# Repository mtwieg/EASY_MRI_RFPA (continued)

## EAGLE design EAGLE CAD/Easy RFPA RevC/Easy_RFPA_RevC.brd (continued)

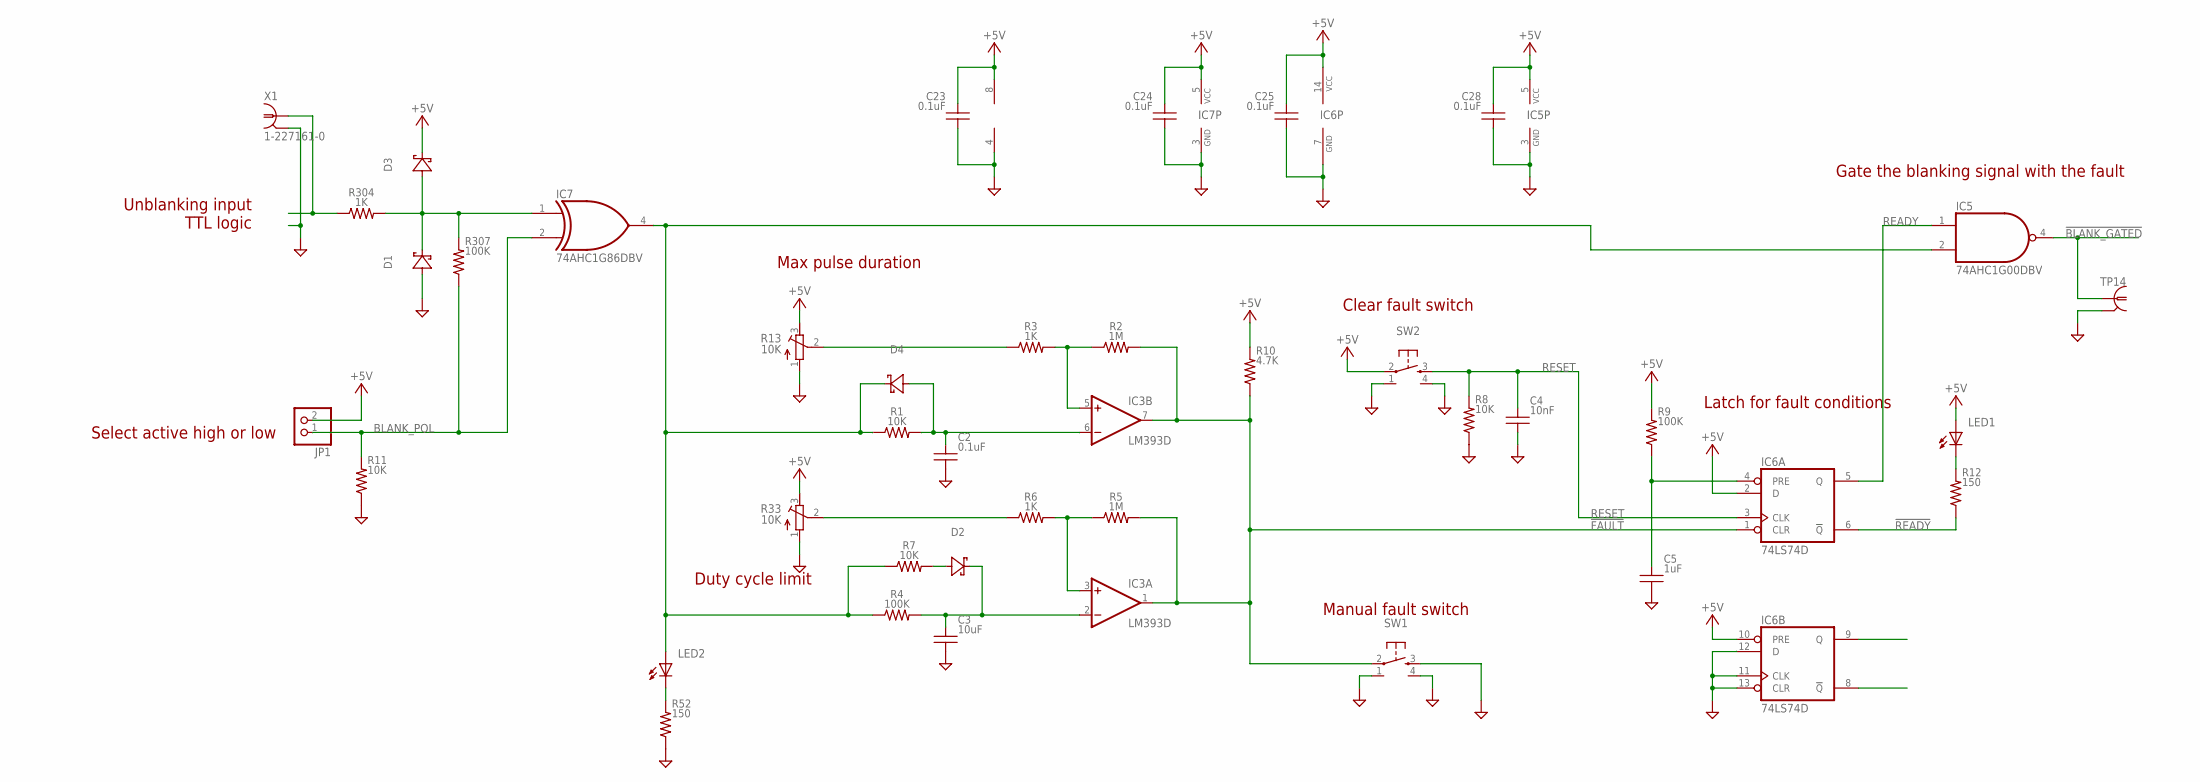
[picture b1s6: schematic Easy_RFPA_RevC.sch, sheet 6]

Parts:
C2, C23, C24, C25, C28: 0.1uF; 0805_IPC-7351B; VOLTAGE 25V
C3: 10uF; 0805_IPC-7351B; VOLTAGE 25V
C4: 10nF; 0805_IPC-7351B; VOLTAGE 50V
C5: 1uF; 0805_IPC-7351B; VOLTAGE 50V
D1, D2, D3, D4: D-SCHOTTKY1N5711W-7-FSOD123; SOD123
IC3: LM393D; SO08
IC5: 74AHC1G00DBV; SOT23-5
IC6: 74LS74D; SO14
IC7: 74AHC1G86DBV; SOT23-5
JP1: PINHD-1X2; 1X02
LED1, LED2: LEDT1_3/4_RA; LED_5MM_RA
R1, R7, R8, R11: 10K; 0805_IPC-7351B
R2, R5: 1M; 0805_IPC-7351B
R3, R6, R304: 1K; 0805_IPC-7351B
R4, R9, R307: 100K; 0805_IPC-7351B
R10: 4.7K; 0805_IPC-7351B
R12, R52: 150; 0805_IPC-7351B
R13, R33: 10K; RTRIM3299W
SW1, SW2: SPST_NO_TACT_RA431256083716431256083716; 431256083716
TP14: PROBE_TPTP_5MM; PROBE_TP_5MM
X1: 1-227161-0; AMP_227161

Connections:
!BLANK_GATED: IC5.4 (O), TP14.TP (1); also elsewhere on the board
!FAULT: IC3.1 (OUT), IC3.7 (OUT), IC6.1 (CLR), R2.2, R5.2, R10.2, SW1.2 (P1)
!READY: IC6.6 (!Q), R12.2
+5V: C23.1, C24.1, C25.1, C28.1, D3.K (C1), IC3.8 (V+), IC5.5 (VCC), IC6.2 (D), IC6.10 (PRE), IC6.14 (VCC), IC7.5 (VCC), JP1.2, LED1.A, R9.1, R10.1, R13.3 (E), R33.3 (E), SW2.2 (P1); also elsewhere on the board
BLANK_POL: IC7.2 (I1), JP1.1, R11.1, R307.2
GND: C2.2, C3.2, C4.2, C5.2, C23.2, C24.2, C25.2, C28.2, D1.A (A1), IC3.4 (V-), IC5.3 (GND), IC6.7 (GND), IC6.11 (CLK), IC6.12 (D), IC6.13 (CLR), IC7.3 (GND), R8.2, R11.2, R13.1 (A), R33.1 (A), R52.2, SW1.1 (G1), SW1.3 (S1), SW1.4 (G2), SW2.1 (G1), SW2.4 (G2), TP14.GND (GND1), X1.2; also elsewhere on the board
unnamed: D1.K (C1), D3.A (A1), IC7.1 (I0), R304.2, R307.1
unnamed: R304.1, X1.1
unnamed: C2.1, D4.A (A1), IC3.6 (-IN), R1.2
unnamed: C5.1, IC6.4 (PRE), R9.2
unnamed: IC3.5 (+IN), R2.1, R3.2
unnamed: R3.1, R13.2 (S)
unnamed: C3.1, D2.K (C1), IC3.2 (-IN), R4.2
unnamed: IC3.3 (+IN), R5.1, R6.2
unnamed: R6.1, R33.2 (S)
unnamed: D4.K (C1), IC5.2 (I1), IC7.4 (O), LED2.A, R1.1, R4.1, R7.1
unnamed: D2.A (A1), R7.2
unnamed: LED2.K (C), R52.1
unnamed: LED1.K (C), R12.1
READY: IC5.1 (I0), IC6.5 (Q)
RESET: C4.1, IC6.3 (CLK), R8.1, SW2.3 (S1)

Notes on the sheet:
Unblanking input TTL logic
Select active high or low
Max pulse duration
Duty cycle limit
Manual fault switch
Clear fault switch
Latch for fault conditions
Gate the blanking signal with the fault

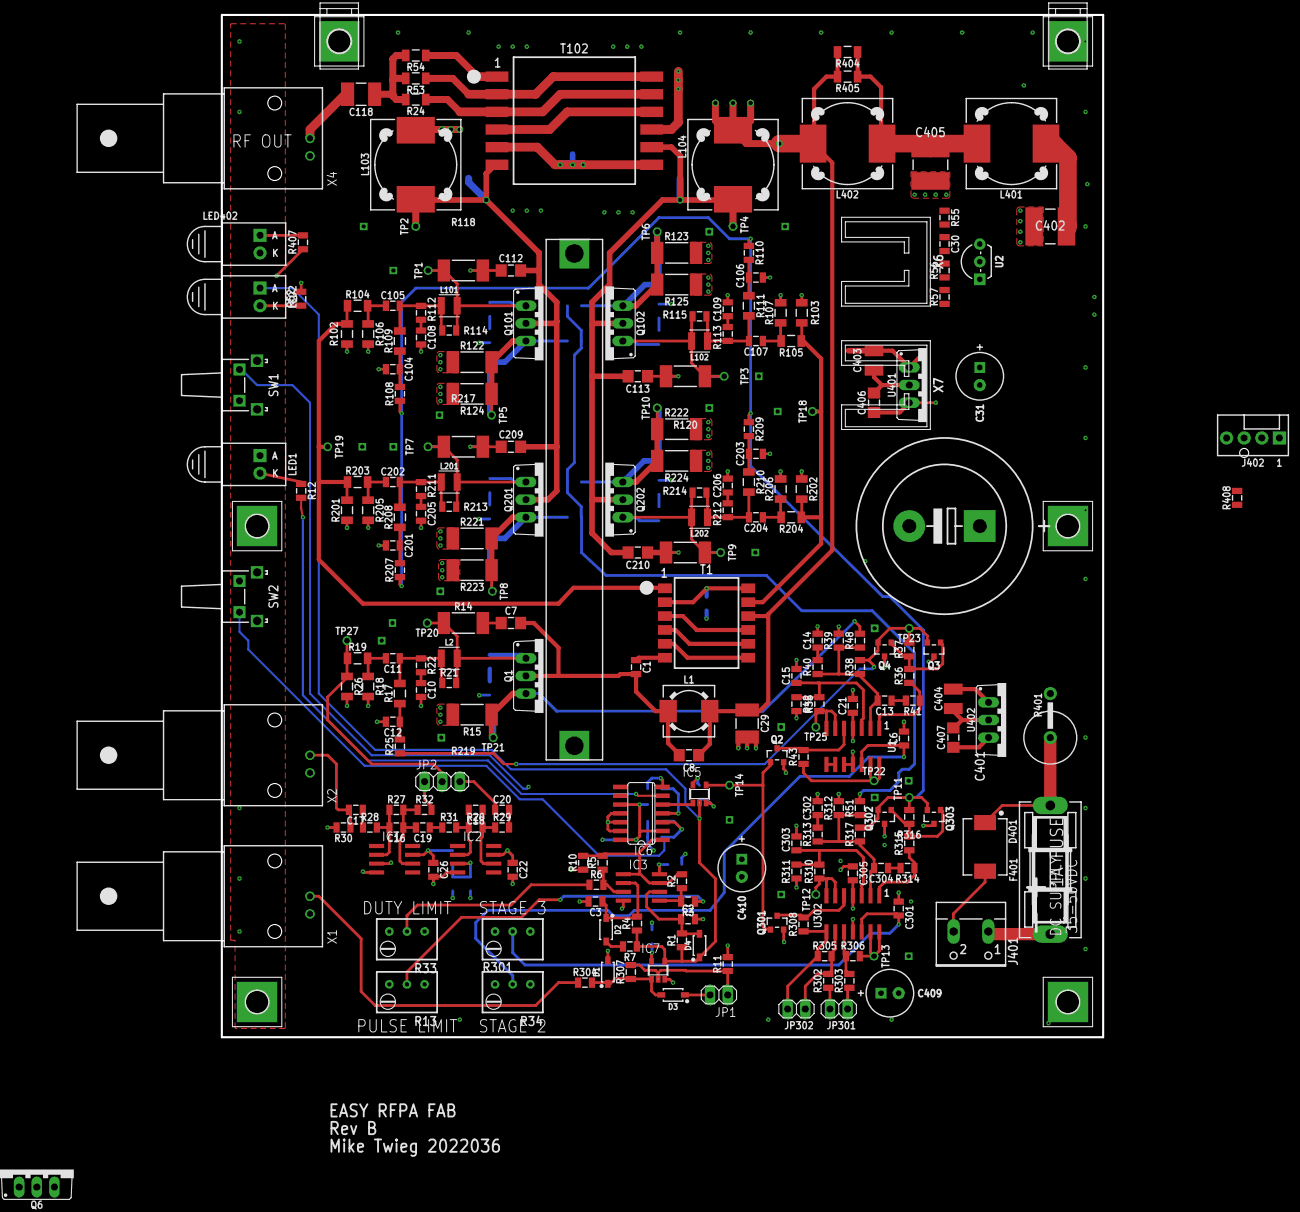
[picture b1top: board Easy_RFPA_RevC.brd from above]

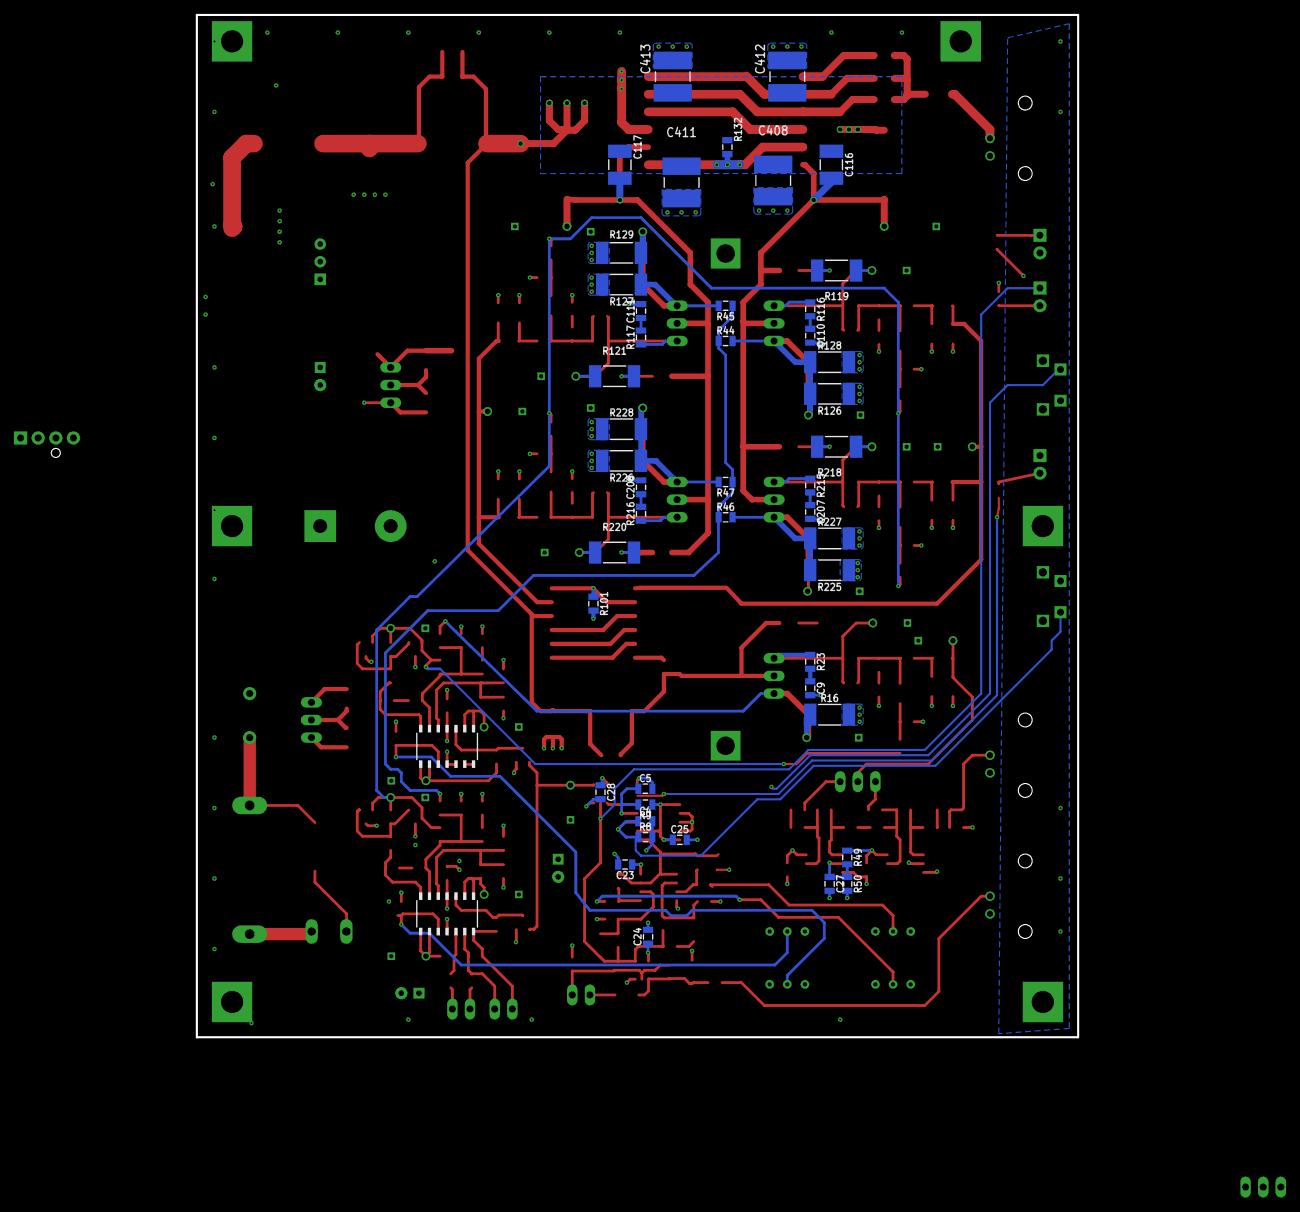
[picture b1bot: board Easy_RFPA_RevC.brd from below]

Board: 4 copper layers, 127.0 x 147.3 mm, 296 parts (46 on the bottom side), 130 nets.

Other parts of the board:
U$1, U$2: KEYSTONE_634

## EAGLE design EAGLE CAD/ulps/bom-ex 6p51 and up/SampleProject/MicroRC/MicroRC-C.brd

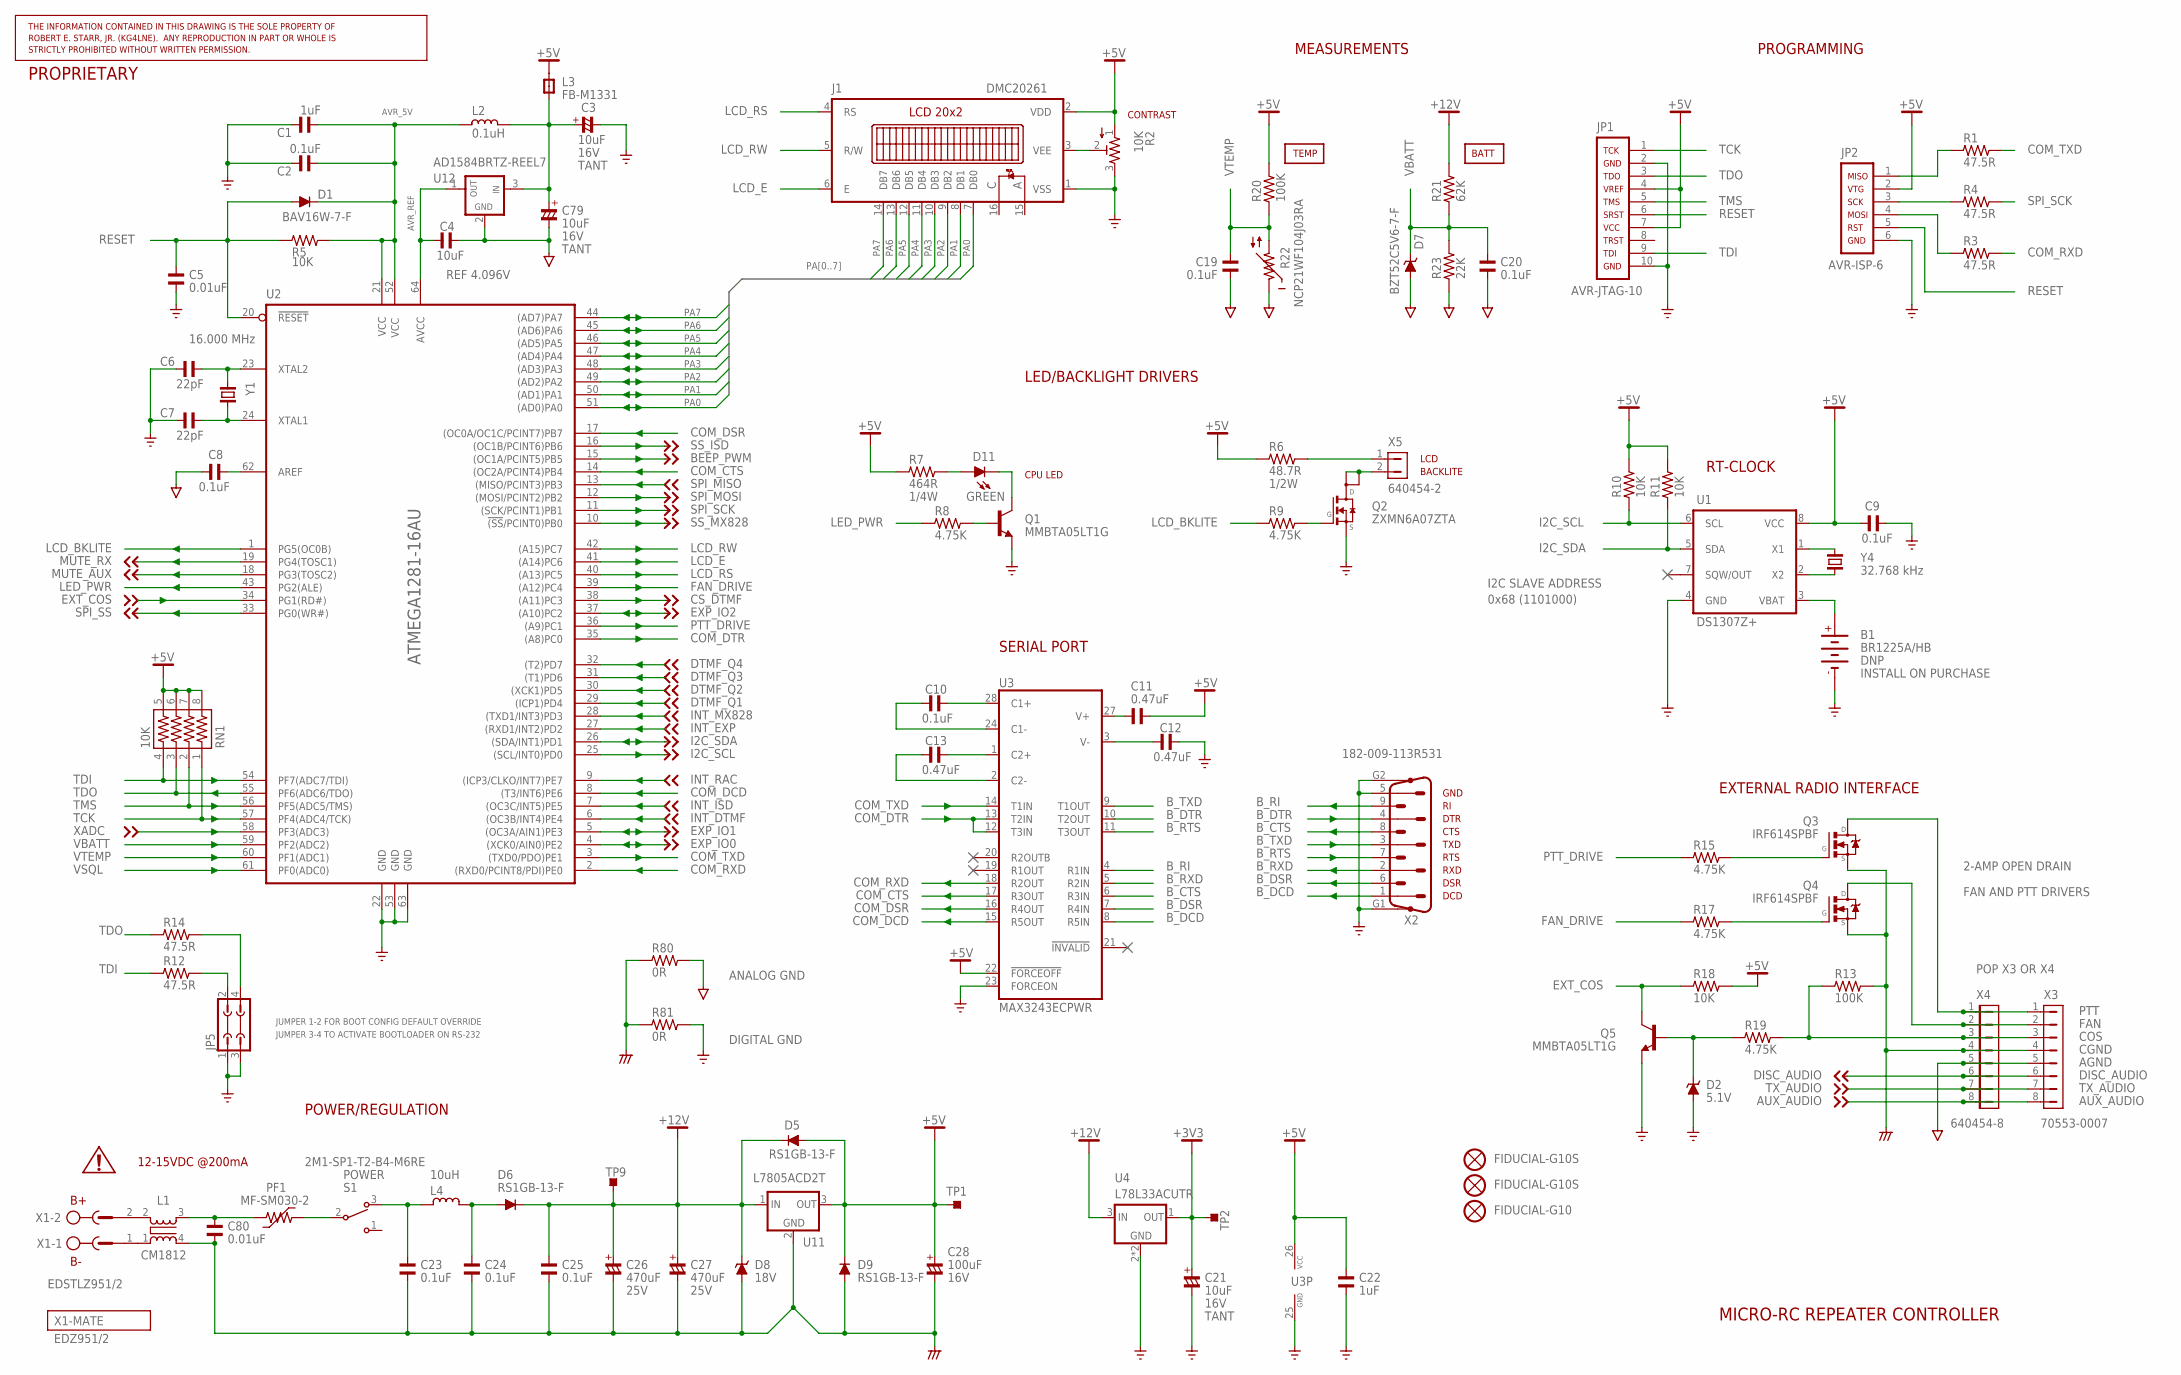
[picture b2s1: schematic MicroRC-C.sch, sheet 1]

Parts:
B1: BR1225A/HB; BR1225; PARTNO BR1225A/HB
C1, C22: 1uF; C0805; PARTNO C0805C105Z3VACTU
C2, C8, C9, C10, C19, C20: 0.1uF; C0805; PARTNO C0805F104K5RACTU
C3, C21, C79: 10uF; C3528/T; PARTNO T491B106M016AT
C4: 10uF; C0805; PARTNO C0805C106K9PACTU
C5: 0.01uF; C0805; PARTNO C0805C103K5RACTU
C6, C7: 22pF; C0805; PARTNO C0805C220J5GACTU
C11, C12, C13: 0.47uF; C0805; PARTNO C0805F474K3RACTU
C23, C24, C25: 0.1uF; C1206; PARTNO C1206C104K5RACTU
C26, C27: 470uF; CSV-G; PARTNO EEE-1EA471P
C28: 100uF; CSV-E/F; PARTNO EEE-1CA101P
C80: 0.01uF; C1206; PARTNO 12065C103KAT2A
D1: BAV16W-7-F; SOD123; PARTNO BAV16W-7-F
D2: 5.1V; SOD123; PARTNO BZT52C5V1-7-F
D5, D6, D9: RS1GB-13-F; SMB; PARTNO RS1GB-13-F
D7: BZT52C5V6-7-F; SOD123; PARTNO BZT52C5V6-7-F
D8: 18V; SMB; PARTNO 1SMB5931BT3G
D11: GREEN; LED535; PARTNO 5350T5
FIDUCIAL1, FIDUCIAL2: FIDUCIAL-G10S; G10S
FIDUCIAL3: FIDUCIAL-G10; G10
J1: DMC20261; PARTNO *
JP1: AVR-JTAG-10; PARTNO *
JP2: AVR-ISP-6
JP5: JP2Q; PARTNO *
L1: CM1812; PARTNO CM1812R600R-10
L2: 0.1uH; L1206; PARTNO PM1210-R10J
L3: FB-M1331; L1206; PARTNO PM2001-200
L4: 10uH; PM-13; PARTNO PM3308-100M
PF1: MF-SM030-2; SMD-7555; PARTNO MF-SM030-2
Q1, Q5: MMBTA05LT1G; SOT23; PARTNO MMBTA05LT1G
Q2: ZXMN6A07ZTA; SOT89; PARTNO ZXMN6A07ZTA
Q3, Q4: IRF614SPBF; D2PAK; PARTNO IRF614SPBF
R1, R3, R4, R12, R14: 47.5R; R0805; PARTNO ERJ-6ENF47R5V
R2: 10K; EVM-L4G; PARTNO EVM-L4GA00B14
R5, R10, R11, R18: 10K; R0805; PARTNO ERJ-6ENF1002V
R6: 48.7R; R2010; PARTNO ERJ-12SF48R7U
R7: 464R; R1210; PARTNO ERJ-14NF4640U
R8, R9, R15, R17, R19: 4.75K; R0805; PARTNO ERJ-6ENF4751V
R13, R20: 100K; R0805; PARTNO ERJ-6ENF1003V
R21: 62K; R0805; PARTNO ERJ-6ENF6192V
R22: NCP21WF104J03RA; R0805; PARTNO NCP21WF104J03RA
R23: 22K; R0805; PARTNO ERJ-6ENF2212V
R80, R81: 0R; R0805; PARTNO RC0805JR-070RL
RN1: 10K; 744-8; PARTNO 744C083103JPTR
S1: 2M1-SP1-T2-B4-M6RE; CK-A; PARTNO 2M1-SP1-T2-B4-M6RE
TP1, TP2, TP9: TPTP10SQ; TP10SQ
U1: DS1307Z+; SO08; PARTNO DS1307Z+
U2: ATMEGA1281-16AU; TQFP64-AEB; PARTNO ATMEGA1281-16AU
U3: MAX3243ECPWR; TSSOP28; PARTNO MAX3243ECPWR
U4: L78L33ACUTR; SOT89-4; PARTNO L78L33ACUTR
U11: L7805ACD2T; D2PAK; PARTNO L7805ACD2T
U12: AD1584BRTZ-REEL7; SOT23; PARTNO AD1584BRTZ-REEL7
X1: EDSTLZ951/2; 951-2; PARTNO EDSTLZ951/2
X2: 182-009-113R531; NC182M9; PARTNO 182-009-113R531
X3: 70553-0007; 70553-08; PARTNO 70553-0007
X4: 640454-8; MTA08-100; PARTNO 640454-8
X5: 640454-2; MTA-100-2V; PARTNO 640454-2
Y1: 16.000 MHz; TC38H; PARTNO ECS-160-18-9X
Y4: 32.768 kHz; TC26H; PARTNO ECS-.327-12.5-13X

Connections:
+3V3: C21.+, TP2.TP, U4.1 (OUT); also elsewhere on the board
+5V: C9.1, C11.1, C22.1, C28.+, D5.A, D9.C, J1.2 (VDD), JP1.4, JP1.7, JP2.2, L3.2, R2.1, R6.1, R7.1, R10.2, R11.2, R18.2, R20.2, RN1.5, RN1.6, RN1.7, RN1.8, TP1.TP, U1.8 (VCC), U3.22 (!FORCEOFF!), U3.26 (VCC), U11.3 (OUT); also elsewhere on the board
+12V: C25.1, C26.+, C27.+, D5.C, D6.C, D8.C, R21.2, TP9.TP, U4.3 (IN), U11.1 (IN); also elsewhere on the board
AGND: C4.1, C8.2, C19.2, C20.2, C79.-, D7.A, R22.1, R23.1, R80.2, U12.2 (GND), X3.5, X4.5; also elsewhere on the board
AUX_AUDIO: X3.8, X4.8; also elsewhere on the board
AVR_5V: C1.1, C2.1, D1.C, L2.2, R5.2, U2.21 (VCC), U2.52 (VCC1)
AVR_REF: C4.2, U2.64 (AVCC), U12.1 (OUT)
BEEP_PWM: U2.15 ((OC1A/PCINT5)PB5); also elsewhere on the board
B_CTS: U3.6 (R3IN), X2.8
B_DCD: U3.8 (R5IN), X2.1
B_DSR: U3.7 (R4IN), X2.6
B_DTR: U3.10 (T2OUT), X2.4
B_RI: U3.4 (R1IN), X2.9
B_RTS: U3.11 (T3OUT), X2.7
B_RXD: U3.5 (R2IN), X2.2
B_TXD: U3.9 (T1OUT), X2.3
CGND: C23.2, C24.2, C25.2, C26.-, C27.-, C28.-, C80.2, D8.A, D9.A, L1.4, Q3.3 (S), Q4.3 (S), R13.2, R80.1, R81.1, U11.2 (GND), X3.4, X4.4
COM_CTS: U2.14 ((OC2A/PCINT4)PB4), U3.17 (R3OUT)
COM_DCD: U2.8 ((T3/INT6)PE6), U3.15 (R5OUT)
COM_DSR: U2.17 ((OC0A/OC1C/PCINT7)PB7), U3.16 (R4OUT)
COM_DTR: U2.35 ((A8)PC0), U3.12 (T3IN), U3.13 (T2IN)
COM_RXD: R3.2, U2.2 ((RXD0/PCINT8/PDI)PE0), U3.18 (R2OUT)
COM_TXD: R1.2, U2.3 ((TXD0/PDO)PE1), U3.14 (T1IN)
COS: R13.1, R19.2, X3.3, X4.3
CS_DTMF: U2.38 ((A11)PC3); also elsewhere on the board
DISC_AUDIO: X3.6, X4.6; also elsewhere on the board
DTMF_Q1: U2.29 ((ICP1)PD4); also elsewhere on the board
DTMF_Q2: U2.30 ((XCK1)PD5); also elsewhere on the board
DTMF_Q3: U2.31 ((T1)PD6); also elsewhere on the board
DTMF_Q4: U2.32 ((T2)PD7); also elsewhere on the board
EXP_IO0: U2.4 ((XCK0/AIN0)PE2); also elsewhere on the board
EXP_IO1: U2.5 ((OC3A/AIN1)PE3); also elsewhere on the board
EXP_IO2: U2.37 ((A10)PC2); also elsewhere on the board
EXT_COS: Q5.3 (C), R18.1, U2.34 (PG1(RD#))
FAN: Q4.2 (D), X3.2, X4.2
FAN_DRIVE: R17.1, U2.39 ((A12)PC4)
GND: B1.-, C1.2, C2.2, C3.-, C5.2, C6.2, C7.2, C9.2, C12.1, C21.-, C22.2, D2.A, J1.1 (VSS), JP1.2, JP1.10, JP2.6, JP5.1, JP5.3, Q1.2 (E), Q2.3 (S), Q5.2 (E), R2.3, R81.2, U1.4 (GND), U2.22 (GND), U2.53 (GND1), U2.63 (GND2), U3.23 (FORCEON), U3.25 (GND), U4.2 (GND), U4.4 (GND), X2.5, X2.G1, X2.G2; also elsewhere on the board
I2C_SCL: R10.1, U1.6 (SCL), U2.25 ((SCL/INT0)PD0); also elsewhere on the board
I2C_SDA: R11.1, U1.5 (SDA), U2.26 ((SDA/INT1)PD1); also elsewhere on the board
INT_DTMF: U2.6 ((OC3B/INT4)PE4); also elsewhere on the board
INT_EXP: U2.27 ((RXD1/INT2)PD2); also elsewhere on the board
INT_ISD: U2.7 ((OC3C/INT5)PE5); also elsewhere on the board
INT_MX828: U2.28 ((TXD1/INT3)PD3); also elsewhere on the board
INT_RAC: U2.9 ((ICP3/CLKO/INT7)PE7); also elsewhere on the board
LCD_BKLITE: R9.1, U2.1 (PG5(OC0B))
LCD_E: J1.6 (E), U2.41 ((A14)PC6)
LCD_RS: J1.4 (RS), U2.40 ((A13)PC5)
LCD_RW: J1.5 (R/W), U2.42 ((A15)PC7)
LED_PWR: R8.1, U2.43 (PG2(ALE))
MUTE_AUX: U2.18 (PG3(TOSC2)); also elsewhere on the board
MUTE_RX: U2.19 (PG4(TOSC1)); also elsewhere on the board
unnamed: L1.1, X1.1
unnamed: C8.1, U2.62 (AREF)
unnamed: JP5.2, R12.2
unnamed: C23.1, L4.1, S1.3 (O)
unnamed: L1.2, X1.2
unnamed: C24.1, D6.A, L4.2
unnamed: U1.1 (X1), Y4.2
unnamed: U1.2 (X2), Y4.1
unnamed: C7.1, U2.24 (XTAL1), Y1.1
unnamed: JP5.4, R14.2
unnamed: C12.2, U3.3 (V-)
unnamed: C11.2, U3.27 (V+)
unnamed: C6.1, U2.23 (XTAL2), Y1.2
unnamed: C13.1, U3.1 (C2+)
unnamed: C10.1, U3.28 (C1+)
unnamed: C13.2, U3.2 (C2-)
unnamed: C10.2, U3.24 (C1-)
unnamed: B1.+, U1.3 (VBAT)
unnamed: Q3.1 (G), R15.2
unnamed: Q2.1 (G), R9.2
unnamed: Q2.2 (D), Q2.4 (D2), X5.2
unnamed: R6.2, X5.1
unnamed: D2.C, Q5.1 (B), R19.1
unnamed: PF1.2, S1.2
unnamed: Q4.1 (G), R17.2
unnamed: C80.1, L1.3, PF1.1
unnamed: C3.+, C79.+, L2.1, L3.1, U12.3 (IN)
unnamed: D11.K (C), Q1.3 (C)
unnamed: D11.A, R7.2
unnamed: Q1.1 (B), R8.2
unnamed: JP2.1, R1.1
unnamed: JP2.3, R4.1
unnamed: JP2.4, R3.1
PA0: J1.7 (DB0), U2.51 ((AD0)PA0)
PA1: J1.8 (DB1), U2.50 ((AD1)PA1)
PA2: J1.9 (DB2), U2.49 ((AD2)PA2)
PA3: J1.10 (DB3), U2.48 ((AD3)PA3)
PA4: J1.11 (DB4), U2.47 ((AD4)PA4)
PA5: J1.12 (DB5), U2.46 ((AD5)PA5)
PA6: J1.13 (DB6), U2.45 ((AD6)PA6)
PA7: J1.14 (DB7), U2.44 ((AD7)PA7)
PTT: Q3.2 (D), X3.1, X4.1
PTT_DRIVE: R15.1, U2.36 ((A9)PC1)
RESET: C5.1, D1.A, JP1.6, JP2.5, R5.1, U2.20 (!RESET!)
SPI_MISO: U2.13 ((MISO/PCINT3)PB3); also elsewhere on the board
SPI_MOSI: U2.12 ((MOSI/PCINT2)PB2); also elsewhere on the board
SPI_SCK: R4.2, U2.11 ((SCK/PCINT1)PB1); also elsewhere on the board
SPI_SS: U2.33 (PG0(WR#)); also elsewhere on the board
SS_ISD: U2.16 ((OC1B/PCINT6)PB6); also elsewhere on the board
SS_MX828: U2.10 (!(SS!/PCINT0)PB0); also elsewhere on the board
TCK: JP1.1, RN1.1, U2.57 (PF4(ADC4/TCK))
TDI: JP1.9, R12.1, RN1.4, U2.54 (PF7(ADC7/TDI))
TDO: JP1.3, R14.1, RN1.3, U2.55 (PF6(ADC6/TDO))
TMS: JP1.5, RN1.2, U2.56 (PF5(ADC5/TMS))
TX_AUDIO: X3.7, X4.7; also elsewhere on the board
VBATT: C20.1, D7.C, R21.1, R23.2, U2.59 (PF2(ADC2))
VEE_LCD: J1.3 (VEE), R2.2
VSQL: U2.61 (PF0(ADC0)); also elsewhere on the board
VTEMP: C19.1, R20.1, R22.2, U2.60 (PF1(ADC1))
XADC: U2.58 (PF3(ADC3)); also elsewhere on the board

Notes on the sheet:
MICRO-RC REPEATER CONTROLLER
BATT
TEMP
CONTRAST
BACKLITE
LCD
RT-CLOCK
SERIAL PORT
DCD
CPU LED
DSR
RXD
RTS
TXD
CTS
DTR
GND
MEASUREMENTS
POWER/REGULATION
EXTERNAL RADIO INTERFACE
LED/BACKLIGHT DRIVERS
PROGRAMMING
12-15VDC @200mA
POWER
ANALOG GND
DIGITAL GND
2-AMP OPEN DRAIN
FAN AND PTT DRIVERS
REF 4.096V
JUMPER 1-2 FOR BOOT CONFIG DEFAULT OVERRIDE
JUMPER 3-4 TO ACTIVATE BOOTLOADER ON RS-232
I2C SLAVE ADDRESS
0x68 (1101000)

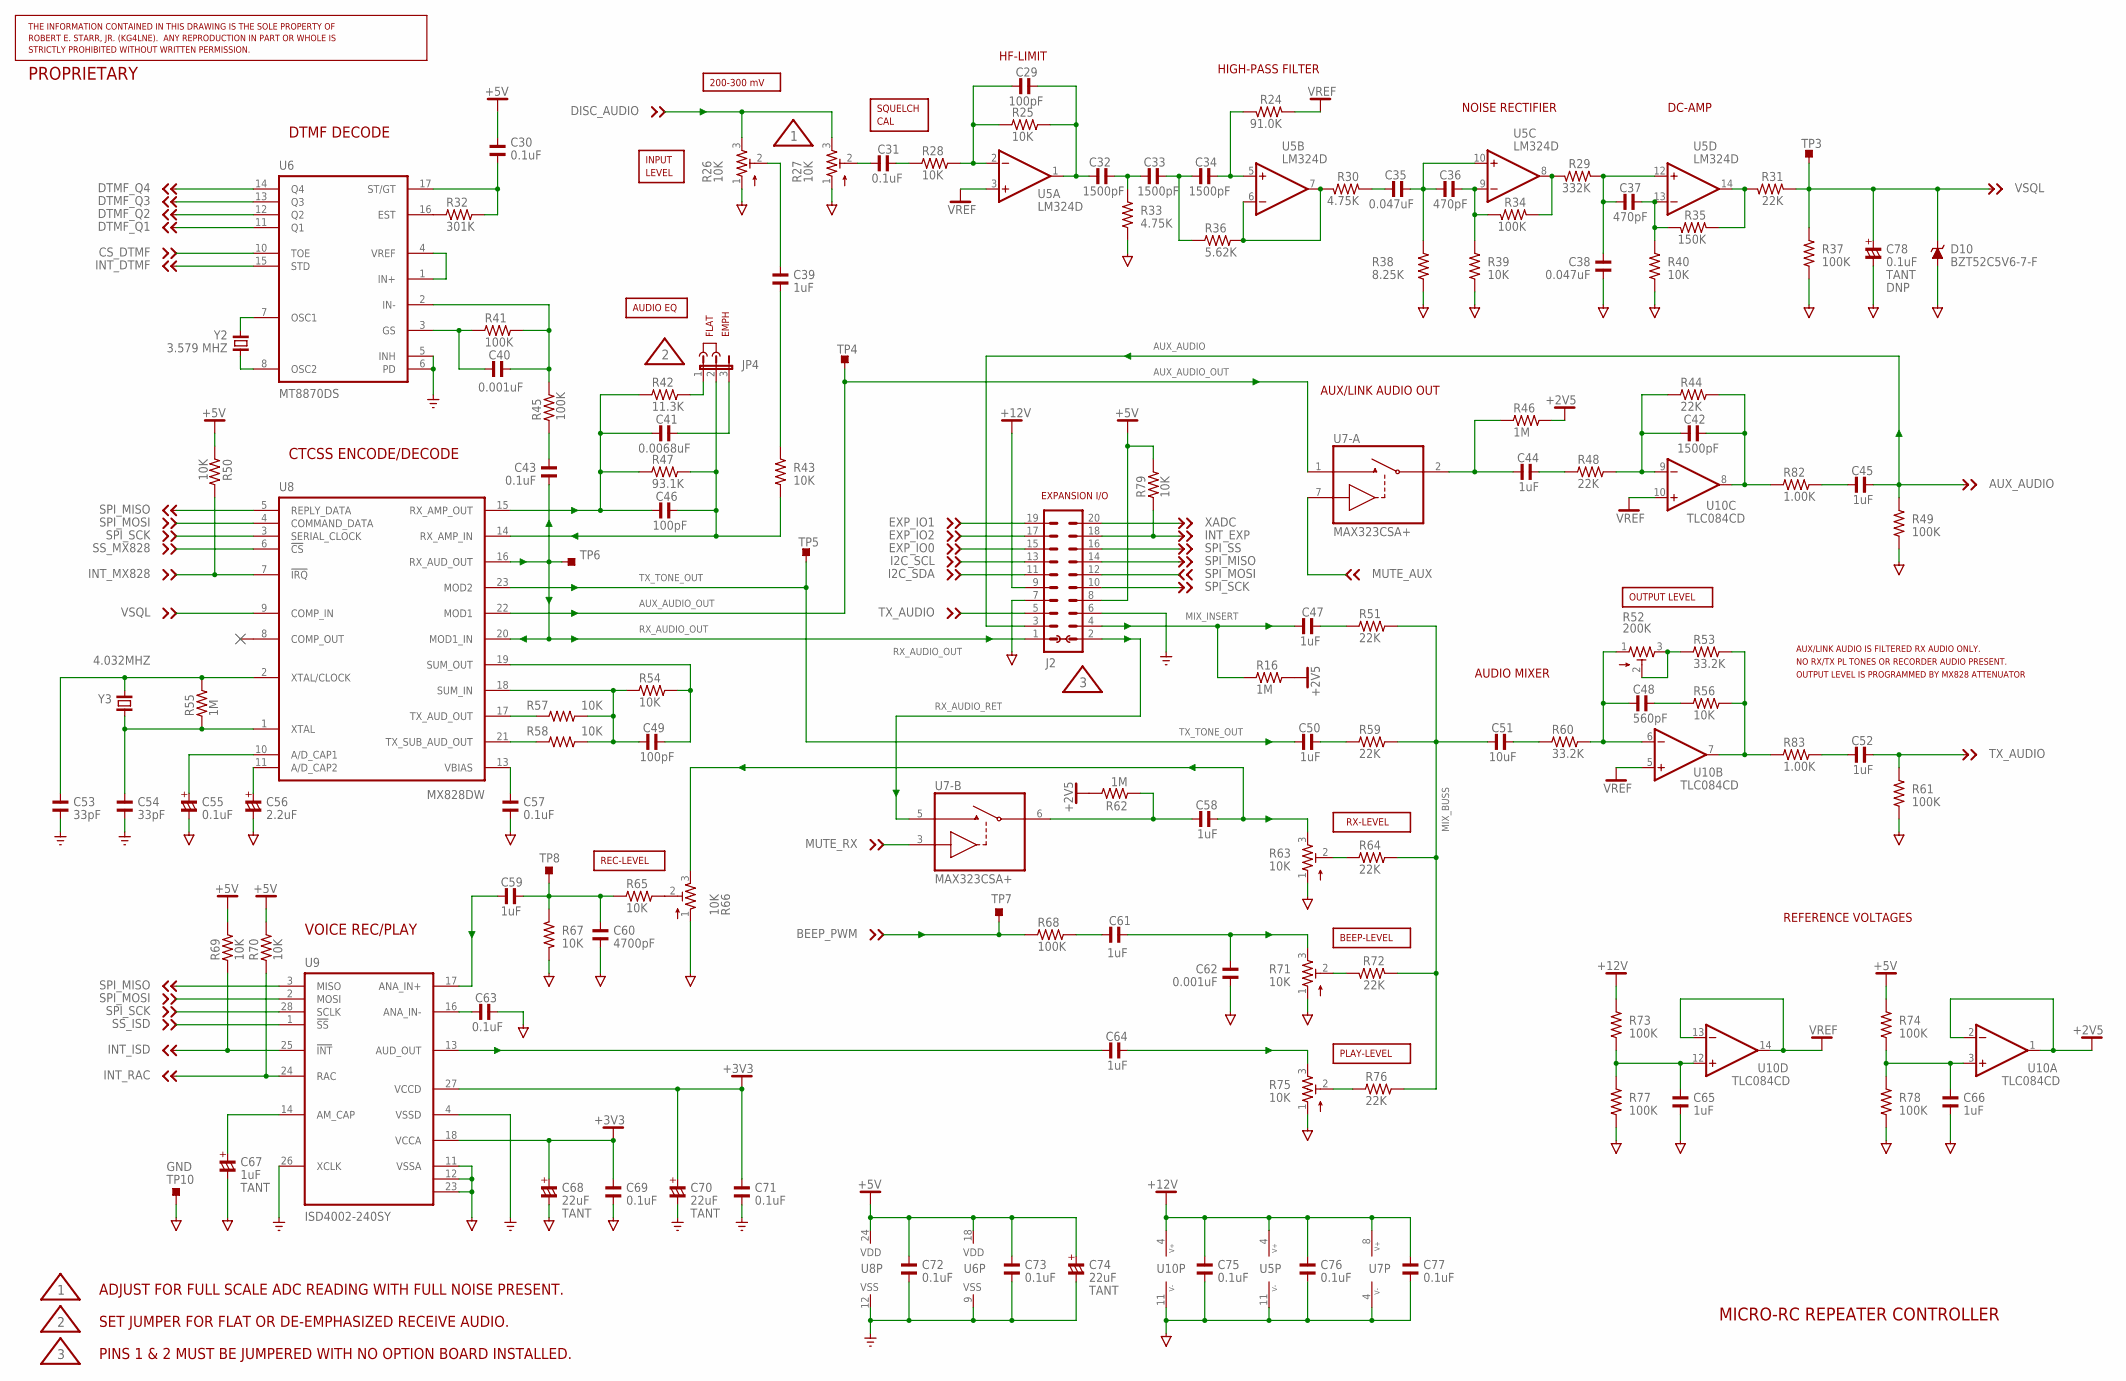
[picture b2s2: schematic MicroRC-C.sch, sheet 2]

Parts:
C29, C46, C49: 100pF; C0805; PARTNO C0805C101J5GACTU
C30, C31, C43, C57, C63, C69, C71, C72, C73, C75, C76, C77: 0.1uF; C0805; PARTNO C0805F104K5RACTU
C32, C33, C34, C42: 1500pF; C0805; PARTNO C0805C152K5RACTU
C35, C38: 0.047uF; C0805; PARTNO C0805C473K5RACTU
C36, C37: 470pF; C0805; PARTNO C0805C471J5GACTU
C39, C44, C45, C47, C50, C52, C58, C59, C61, C64, C65, C66: 1uF; C0805; PARTNO C0805C105Z3VACTU
C40, C62: 0.001uF; C0805; PARTNO C0805C102K5RACTU
C41: 0.0068uF; C0805; PARTNO C0805C682K5RACTU
C48: 560pF; C0805; PARTNO C0805C561J5GACTU
C51: 10uF; C0805; PARTNO C0805C106K9PACTU
C53, C54: 33pF; C0805; PARTNO C0805C330J5GACTU
C55: 0.1uF; C3216/T; PARTNO T491A104K035AT
C56: 2.2uF; C3216/T; PARTNO T491A225K010AT
C60: 4700pF; C0805; PARTNO C0805C472K5RACTU
C67: 1uF; C3216/T; PARTNO T491A105K016AT
C68, C70, C74: 22uF; C3528/T; PARTNO T491B226M016AT
C78: 0.1uF; C3216/T; PARTNO DNP
D10: BZT52C5V6-7-F; SOD123; PARTNO BZT52C5V6-7-F
J2: MA10-2; PARTNO *
JP4: JP2E; JP2; PARTNO *
R16, R46, R55, R62: 1M; R0805; PARTNO ERJ-6ENF1004V
R24: 91.0K; R0805; PARTNO ERJ-6ENF9092V
R25, R28, R39, R40, R43, R50, R54, R56, R57, R58, R65, R67, R69, R70, R79: 10K; R0805; PARTNO ERJ-6ENF1002V
R26, R27, R63, R71, R75: 10K; EVME-SIDE; PARTNO EVM-EGGA00B14
R29: 332K; R0805; PARTNO ERJ-6ENF3323V
R30, R33: 4.75K; R0805; PARTNO ERJ-6ENF4751V
R31, R44, R48, R51, R59, R64, R72, R76: 22K; R0805; PARTNO ERJ-6ENF2212V
R32: 301K; R0805; PARTNO ERJ-6ENF3013V
R34, R37, R41, R45, R49, R61, R68, R73, R74, R77, R78: 100K; R0805; PARTNO ERJ-6ENF1003V
R35: 150K; R0805; PARTNO ERJ-6ENF1503V
R36: 5.62K; R0805; PARTNO ERJ-6ENF5621V
R38: 8.25K; R0805; PARTNO ERJ-6ENF8251V
R42: 11.3K; R0805; PARTNO ERJ-6ENF1132V
R47: 93.1K; R0805; PARTNO ERJ-6ENF9312V
R52: 200K; EVME-SIDE; PARTNO EVM-EGGA00B25
R53, R60: 33.2K; R0805; PARTNO ERJ-6ENF3322V
R66: 10K; EVM-L4G; PARTNO EVM-L4GA00B14
R82, R83: 1.00K; R0805; PARTNO ERJ-6ENF1001V
TP3, TP4, TP5, TP6, TP7: TPTP10SQ; TP10SQ
TP8, TP10: TPS-SMD-10SN; SMD-10SN
U5: LM324D; SO14; PARTNO LM324D
U6: MT8870DS; SO18W; PARTNO MT8870DS
U7: MAX323CSA+; SO08; PARTNO MAX323CSA+
U8: MX828DW; SSOP24; PARTNO MX828DW
U9: ISD4002-240SY; SO28W; PARTNO ISD4002-240SY
U10: TLC084CD; SO14; PARTNO TLC084CD
Y2: 3.579 MHZ; TC310H; PARTNO ECS-35-18-10X
Y3: 4.032MHZ; SM49; PARTNO ECS-40.3-20-5PX-TR

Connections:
+2V5: R16.2, R46.2, R62.2, U10.1 (OUT), U10.2 (-IN)
+3V3: C68.+, C69.1, C70.+, C71.1, U9.18 (VCCA), U9.27 (VCCD); also elsewhere on the board
+5V: C30.2, C72.1, C73.1, C74.+, J2.8, R50.1, R69.2, R70.2, R74.2, R79.2, U6.18 (VDD), U8.24 (VDD); also elsewhere on the board
+12V: C75.1, C76.1, C77.1, J2.9, R73.2, U5.4 (V+), U7.8 (V+), U10.4 (V+); also elsewhere on the board
AGND: C38.1, C55.-, C56.-, C57.2, C60.2, C62.2, C63.1, C65.2, C66.2, C67.-, C68.-, C69.2, C75.2, C76.2, C77.2, C78.-, D10.A, J2.7, R26.1, R27.1, R33.1, R37.2, R38.2, R39.2, R40.2, R49.1, R61.1, R63.1, R66.1, R67.2, R71.1, R75.1, R77.1, R78.1, TP10.TP, U5.11 (V-), U7.4 (V-), U9.11 (VSSA), U9.12 (VSSA), U9.23 (VSSA), U10.11 (V-); also elsewhere on the board
AUX_AUDIO: C45.2, J2.3, R49.2; also elsewhere on the board
AUX_AUDIO_OUT: TP4.TP, U7.1 (NO), U8.22 (MOD1)
BEEP_PWM: R68.1, TP7.TP; also elsewhere on the board
CS_DTMF: U6.10 (TOE); also elsewhere on the board
DISC_AUDIO: R26.3, R27.3; also elsewhere on the board
DTMF_Q1: U6.11 (Q1); also elsewhere on the board
DTMF_Q2: U6.12 (Q2); also elsewhere on the board
DTMF_Q3: U6.13 (Q3); also elsewhere on the board
DTMF_Q4: U6.14 (Q4); also elsewhere on the board
EXP_IO0: J2.15; also elsewhere on the board
EXP_IO1: J2.19; also elsewhere on the board
EXP_IO2: J2.17; also elsewhere on the board
GND: C53.2, C54.2, C70.-, C71.2, C72.2, C73.2, C74.-, J2.6, U6.5 (INH), U6.6 (PD), U6.9 (VSS), U8.12 (VSS), U9.4 (VSSD), U9.26 (XCLK); also elsewhere on the board
I2C_SCL: J2.13; also elsewhere on the board
I2C_SDA: J2.11; also elsewhere on the board
INT_DTMF: U6.15 (STD); also elsewhere on the board
INT_EXP: J2.18, R79.1; also elsewhere on the board
INT_ISD: R69.1, U9.25 (!INT!); also elsewhere on the board
INT_MX828: R50.2, U8.7 (!IRQ!); also elsewhere on the board
INT_RAC: R70.1, U9.24 (RAC); also elsewhere on the board
MIX_BUSS: C51.1, R51.2, R59.2, R64.2, R72.1, R76.2
MIX_INSERT: C47.1, J2.4, R16.1
MUTE_AUX: U7.7 (IN); also elsewhere on the board
MUTE_RX: U7.3 (IN); also elsewhere on the board
unnamed: C45.1, R82.2
unnamed: C39.2, R26.2
unnamed: C58.1, R62.1, U7.6 (COM)
unnamed: R63.2, R64.1
unnamed: R65.2, R66.2
unnamed: C63.2, U9.16 (ANA_IN-)
unnamed: C56.+, U8.11 (A/D_CAP2)
unnamed: C52.1, R83.2
unnamed: JP4.1, R42.2
unnamed: C59.1, C60.1, R65.1, R67.1, TP8.TP
unnamed: U6.7 (OSC1), Y2.2
unnamed: U6.8 (OSC2), Y2.1
unnamed: U6.1 (IN+), U6.4 (VREF)
unnamed: C61.1, R68.2
unnamed: R75.2, R76.1
unnamed: C65.1, R73.1, R77.2, U10.12 (+IN)
unnamed: C64.2, R75.3
unnamed: C40.2, R41.2, R45.2, U6.2 (IN-)
unnamed: C41.2, JP4.3
unnamed: C40.1, R41.1, U6.3 (GS)
unnamed: C30.1, R32.2, U6.17 (ST/GT)
unnamed: R32.1, U6.16 (EST)
unnamed: C59.2, U9.17 (ANA_IN+)
unnamed: C44.2, R48.1
unnamed: C64.1, U9.13 (AUD_OUT)
unnamed: C43.2, R45.1
unnamed: C55.+, U8.10 (A/D_CAP1)
unnamed: C48.2, R56.1
unnamed: R30.2, R36.2, U5.6 (-IN), U5.7 (OUT)
unnamed: C31.1, R27.2
unnamed: C44.1, R46.1, U7.2 (COM)
unnamed: C61.2, C62.1, R71.3
unnamed: R71.2, R72.2
unnamed: C53.1, R55.2, U8.2 (XTAL/CLOCK), Y3.1
unnamed: C54.1, R55.1, U8.1 (XTAL), Y3.2
unnamed: C49.2, R54.2, U8.19 (SUM_OUT)
unnamed: R53.2, R56.2, R83.1, U10.7 (OUT)
unnamed: C39.1, R43.2
unnamed: C46.2, JP4.2, R43.1, R47.2, U8.14 (RX_AMP_IN)
unnamed: C57.1, U8.13 (VBIAS)
unnamed: C41.1, C46.1, R42.1, R47.1, U8.15 (RX_AMP_OUT)
unnamed: C48.1, R52.1, R60.2, U10.6 (-IN)
unnamed: C58.2, R63.3, R66.3
unnamed: C50.2, R59.1
unnamed: C32.2, C33.1, R33.2
unnamed: R29.2, R34.1, U5.8 (OUT)
unnamed: C36.2, R34.2, R39.1, U5.9 (-IN)
unnamed: R57.1, U8.17 (TX_AUD_OUT)
unnamed: C35.1, R30.1
unnamed: R58.1, U8.21 (TX_SUB_AUD_OUT)
unnamed: C34.2, R24.2, U5.5 (+IN)
unnamed: R52.2, R52.3, R53.1
unnamed: C67.+, U9.14 (AM_CAP)
unnamed: C42.1, R44.1, R48.2, U10.9 (-IN)
unnamed: C42.2, R44.2, R82.1, U10.8 (OUT)
unnamed: C33.2, C34.1, R36.1
unnamed: C49.1, R54.1, R57.2, R58.2, U8.18 (SUM_IN)
unnamed: C47.2, R51.1
unnamed: C29.2, C32.1, R25.2, U5.1 (OUT)
unnamed: C35.2, C36.1, R38.1, U5.10 (+IN)
unnamed: C37.1, C38.2, R29.1, U5.12 (+IN)
unnamed: C29.1, R25.1, R28.2, U5.2 (-IN)
unnamed: C31.2, R28.1
unnamed: C37.2, R35.2, R40.1, U5.13 (-IN)
unnamed: C51.2, R60.1
unnamed: C66.1, R74.1, R78.2, U10.3 (+IN)
unnamed: R31.2, R35.1, U5.14 (OUT)
RX_AUDIO_OUT: C43.1, J2.1, TP6.TP, U8.16 (RX_AUD_OUT), U8.20 (MOD1_IN)
RX_AUDIO_RET: J2.2, U7.5 (NO)
SPI_MISO: J2.14, U8.5 (REPLY_DATA), U9.3 (MISO); also elsewhere on the board
SPI_MOSI: J2.12, U8.4 (COMMAND_DATA), U9.2 (MOSI); also elsewhere on the board
SPI_SCK: J2.10, U8.3 (SERIAL_CLOCK), U9.28 (SCLK); also elsewhere on the board
SPI_SS: J2.16; also elsewhere on the board
SS_ISD: U9.1 (!SS!); also elsewhere on the board
SS_MX828: U8.6 (!CS!); also elsewhere on the board
TX_AUDIO: C52.2, J2.5, R61.2; also elsewhere on the board
TX_TONE_OUT: C50.1, TP5.TP, U8.23 (MOD2)
VREF: R24.1, U5.3 (+IN), U10.5 (+IN), U10.10 (+IN), U10.13 (-IN), U10.14 (OUT)
VSQL: C78.+, D10.C, R31.1, R37.1, TP3.TP, U8.9 (COMP_IN); also elsewhere on the board
XADC: J2.20; also elsewhere on the board

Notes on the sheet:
DTMF DECODE
CTCSS ENCODE/DECODE
REC-LEVEL
BEEP-LEVEL
INPUT
RX-LEVEL
FLAT
EMPH
PLAY-LEVEL
AUDIO EQ
CAL
VOICE REC/PLAY
OUTPUT LEVEL
MICRO-RC REPEATER CONTROLLER
EXPANSION I/O
ADJUST FOR FULL SCALE ADC READING WITH FULL NOISE PRESENT.
SET JUMPER FOR FLAT OR DE-EMPHASIZED RECEIVE AUDIO.
LEVEL
SQUELCH
REFERENCE VOLTAGES
AUDIO MIXER
PINS 1 & 2 MUST BE JUMPERED WITH NO OPTION BOARD INSTALLED.
HIGH-PASS FILTER
HF-LIMIT
NOISE RECTIFIER
200-300 mV
AUX/LINK AUDIO OUT
DC-AMP
NO RX/TX PL TONES OR RECORDER AUDIO PRESENT.
AUX/LINK AUDIO IS FILTERED RX AUDIO ONLY.
OUTPUT LEVEL IS PROGRAMMED BY MX828 ATTENUATOR
